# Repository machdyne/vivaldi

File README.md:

# Vivaldi Motherboard

Vivaldi is a host board that when paired with a [Sechzig](https://github.com/machdyne/sechzig) compute module can function as a personal server, network gateway or firewall.

This repo contains schematics, PCB layouts, pinouts and documentation.

Find more information on the [Vivaldi product page](https://machdyne.com/product/vivaldi-motherboard/).

## Using Vivaldi

Vivaldi requires a Sechzig module to function. **When inserting a Sechzig module, make sure that pin 2 on Vivaldi and pin 2 on the module are both on the same side.**

## Firmware

Mozart has a JTAG and USB CDC interface that are both accessible on the USB-C port. These interfaces are provided by a [fork of pico-dirtyJtag](https://github.com/machdyne/vivaldi/tree/main/firmware). You can update the RP2040 firmware by holding down the BOOT button and then applying power.

To build the firmware from source:

```
$ cd firmware/pico-dirtyJtag
$ mkdir build
$ cmake .. -DPICO_DEFAULT_BOOT_STAGE2_FILE=$PICO_SDK_PATH/src/rp2_common/boot_stage2/boot2_generic_03h.S
$ make
```

## Pinouts

### LVDS Port

Vivaldi has an experimental SATA-style LVDS port. SATA is not supported.

| Pin | Signal |
| --- | ------ |
| 1 | GND |
| 2 | DS2\_P |
| 3 | DS2\_N |
| 4 | GND |
| 5 | DS1\_P |
| 6 | DS1\_N |
| 7 | GND |

## Funding

This project was partially funded through the NGI0 Entrust Fund, a fund established by NLnet with financial support from the European Commission's Next Generation Internet programme.

## License

This project is released under the [CERN-OHL-P](LICENSE.txt) license.

Note: You can use these designs for commercial purposes but we ask that instead of producing exact clones, that you either replace our trademarks and logos with your own or add your own next to ours.

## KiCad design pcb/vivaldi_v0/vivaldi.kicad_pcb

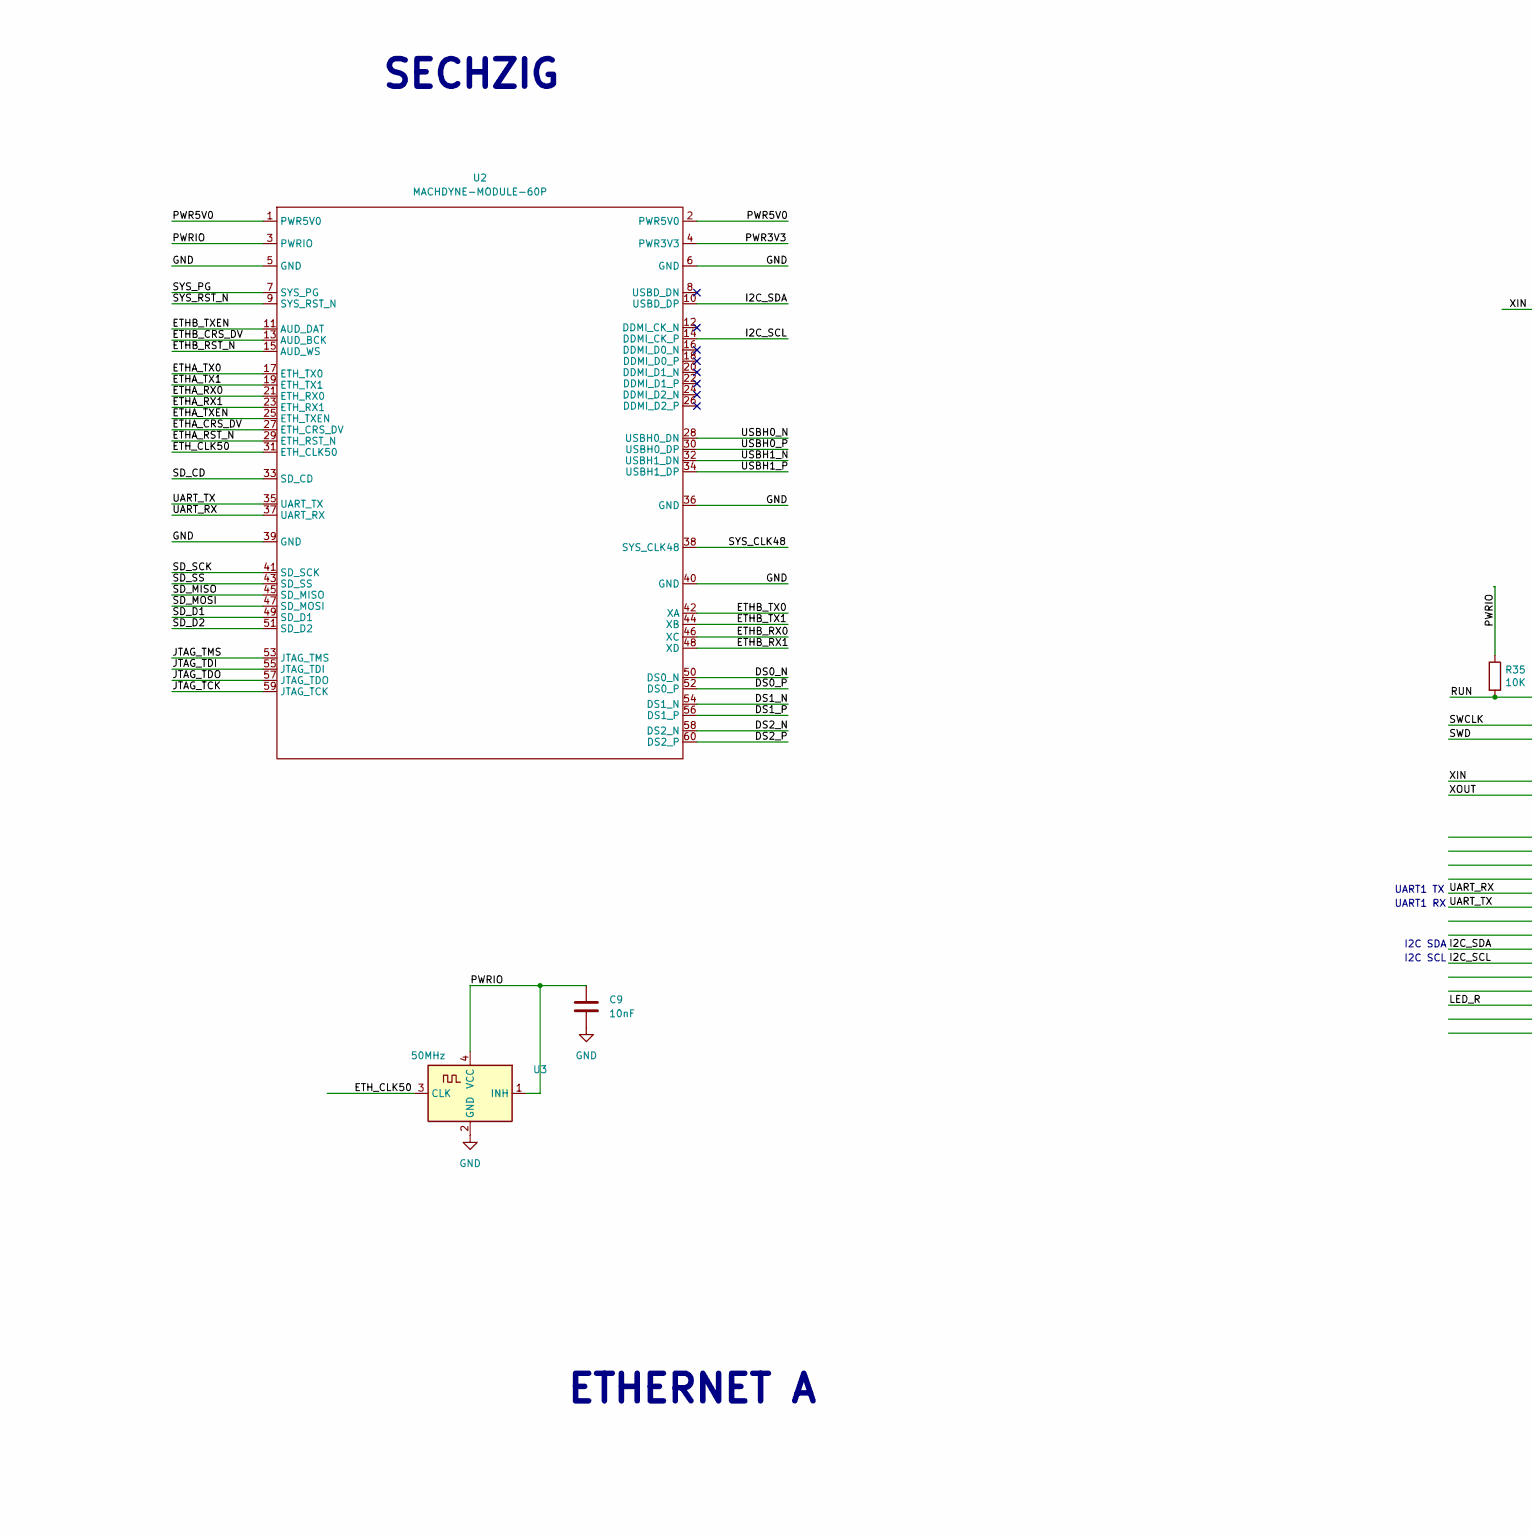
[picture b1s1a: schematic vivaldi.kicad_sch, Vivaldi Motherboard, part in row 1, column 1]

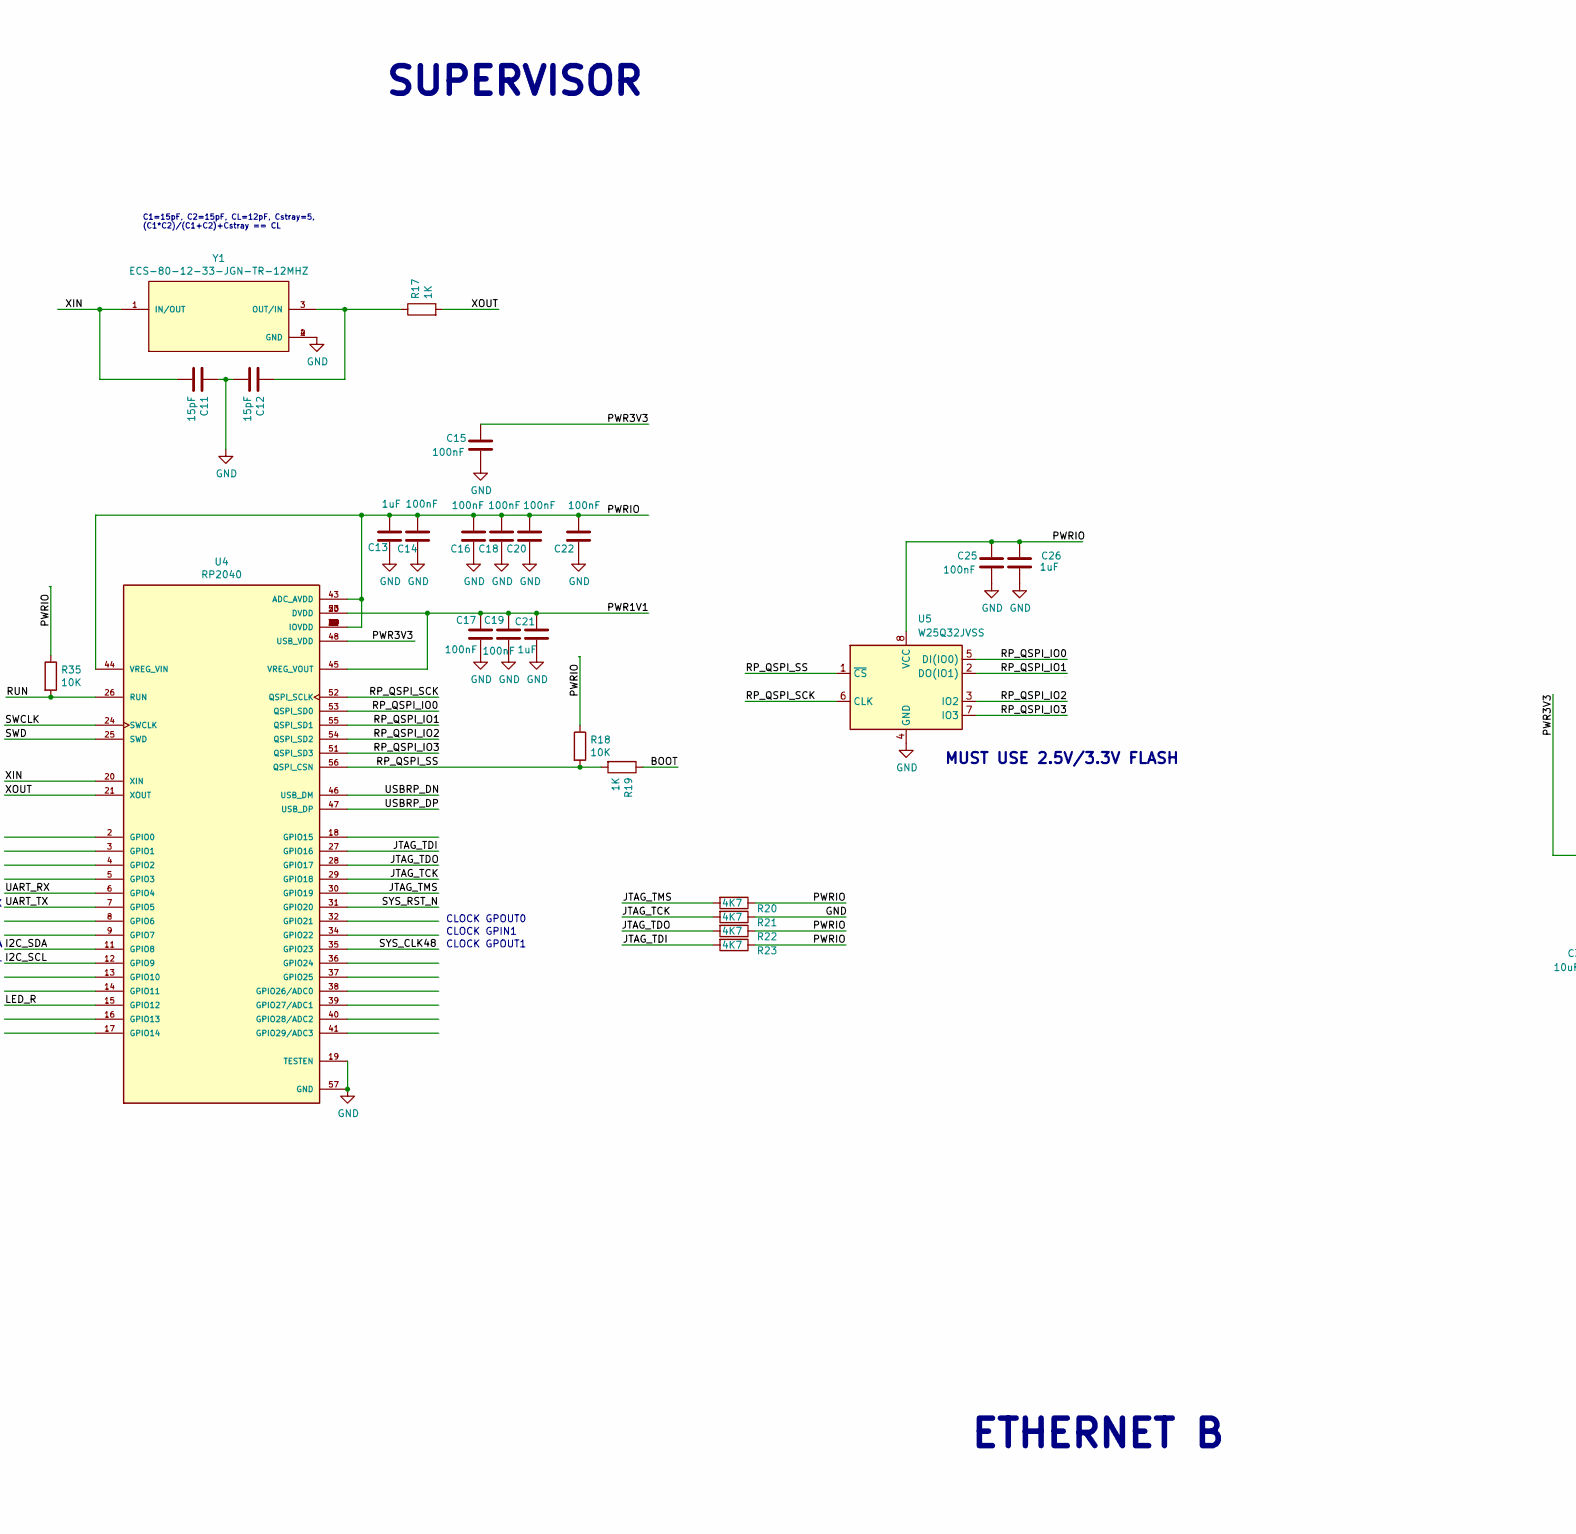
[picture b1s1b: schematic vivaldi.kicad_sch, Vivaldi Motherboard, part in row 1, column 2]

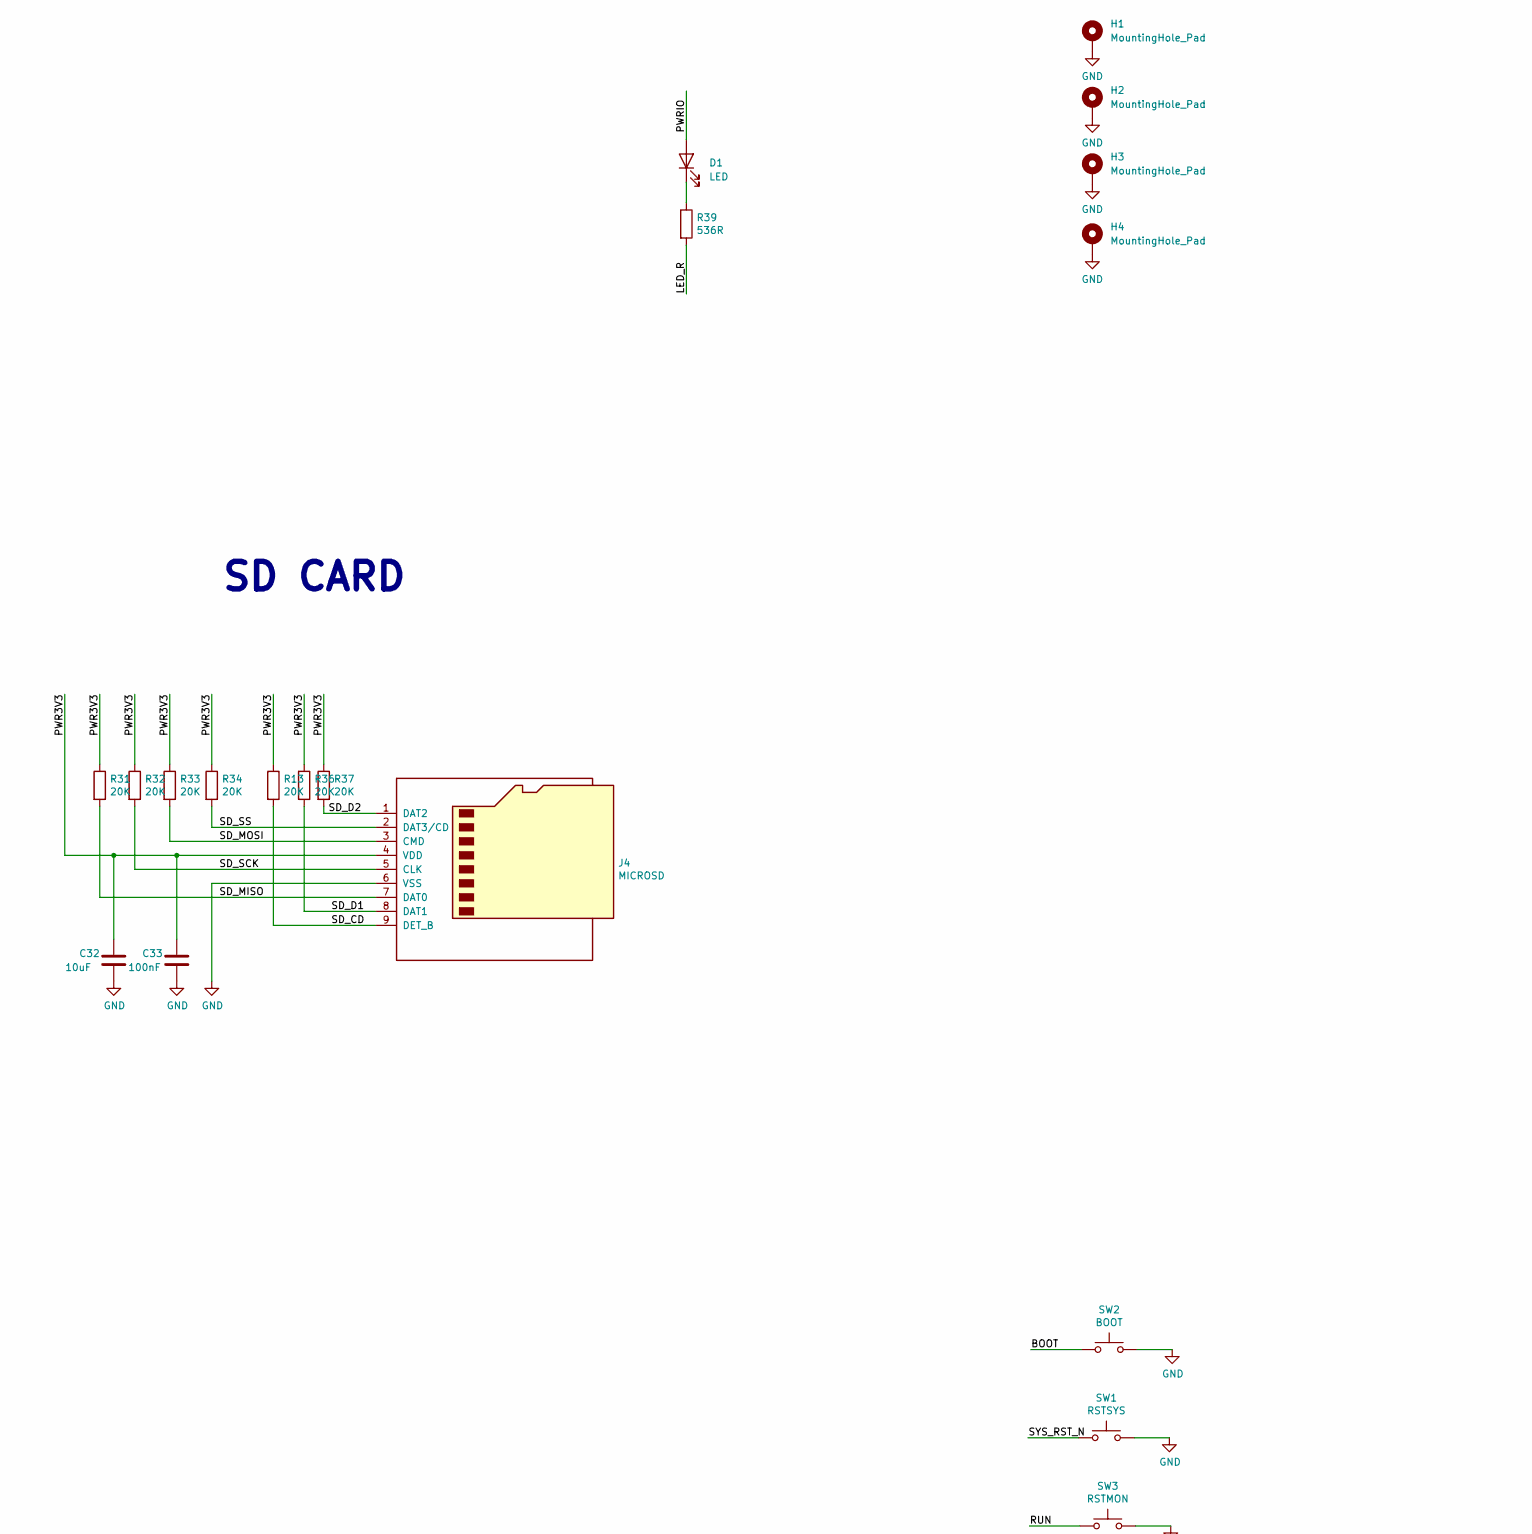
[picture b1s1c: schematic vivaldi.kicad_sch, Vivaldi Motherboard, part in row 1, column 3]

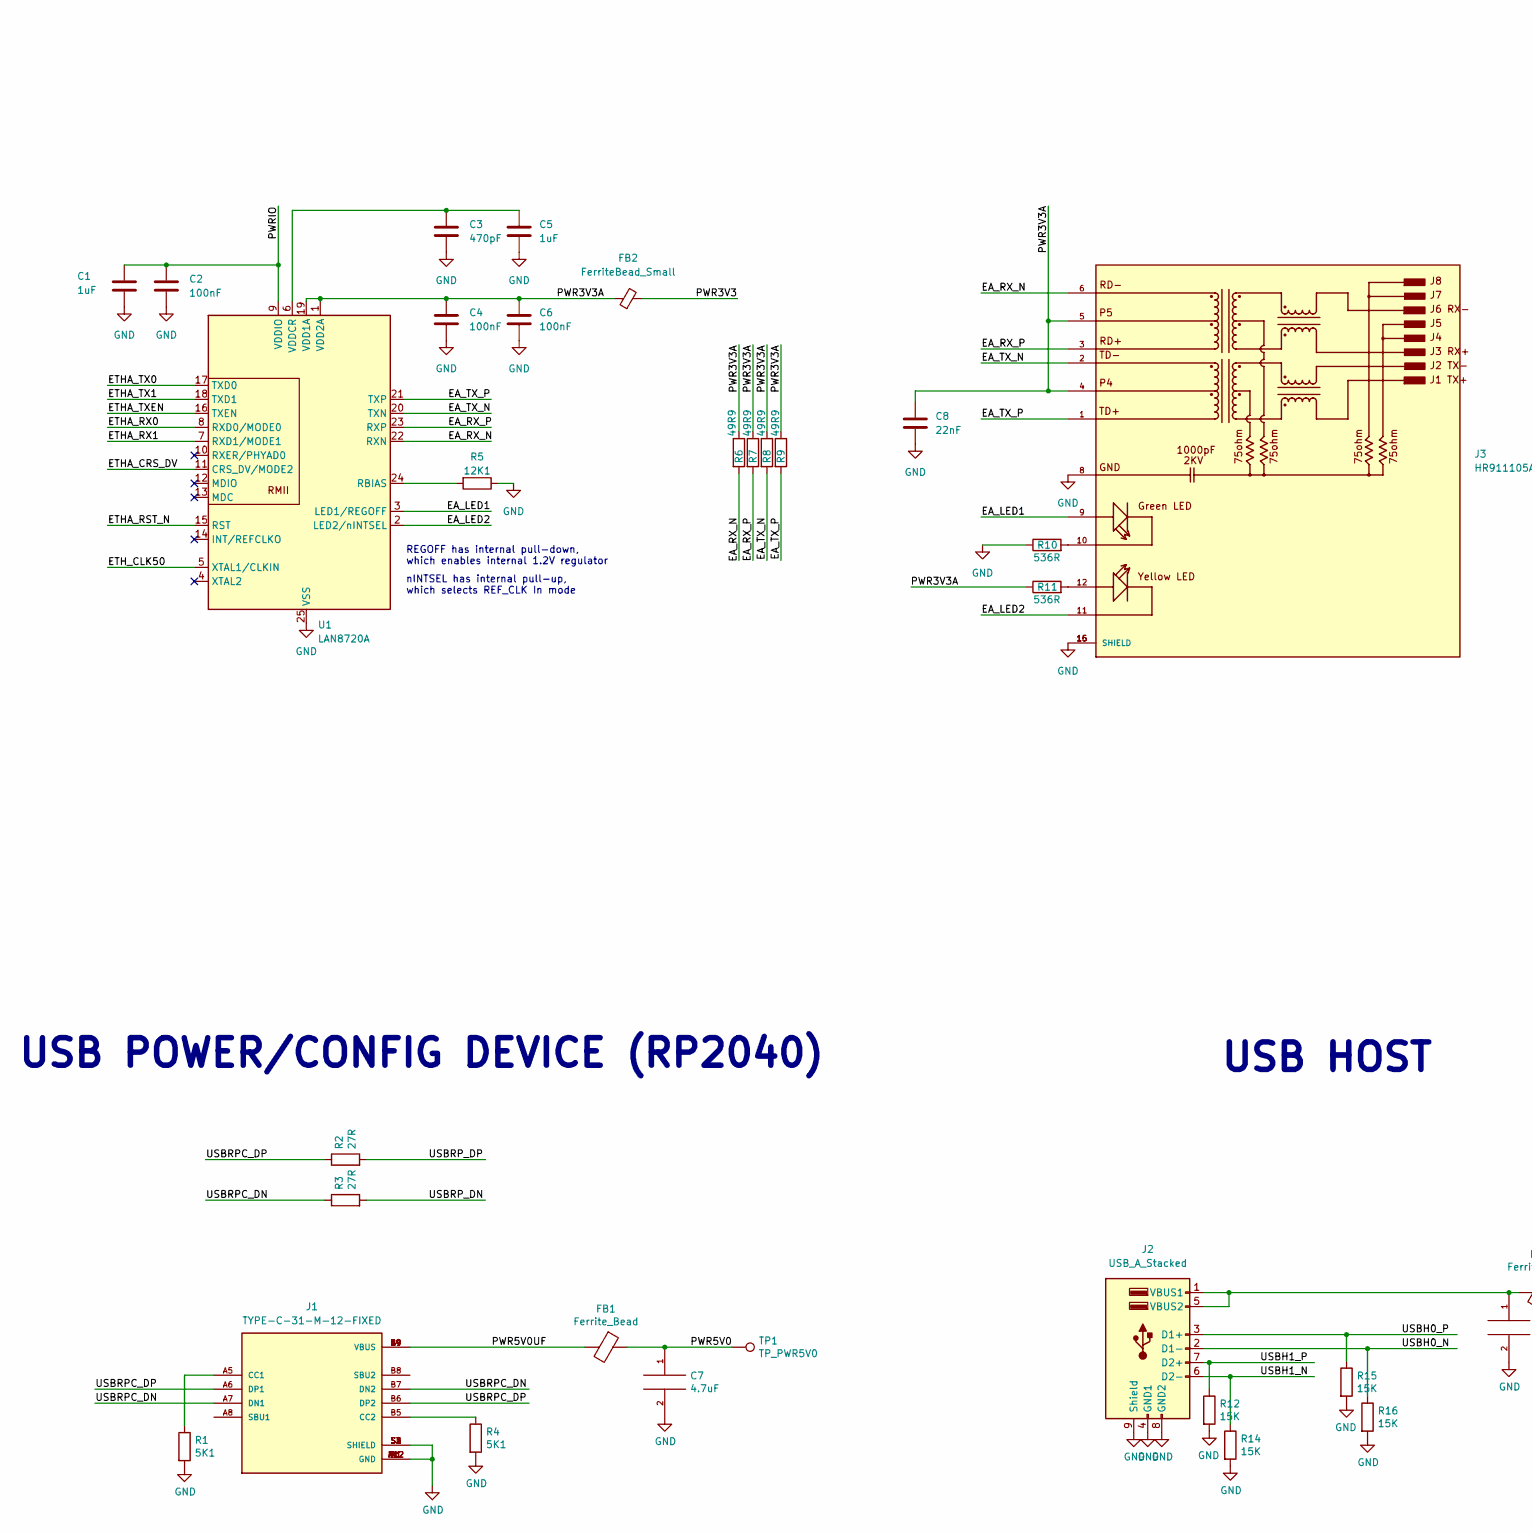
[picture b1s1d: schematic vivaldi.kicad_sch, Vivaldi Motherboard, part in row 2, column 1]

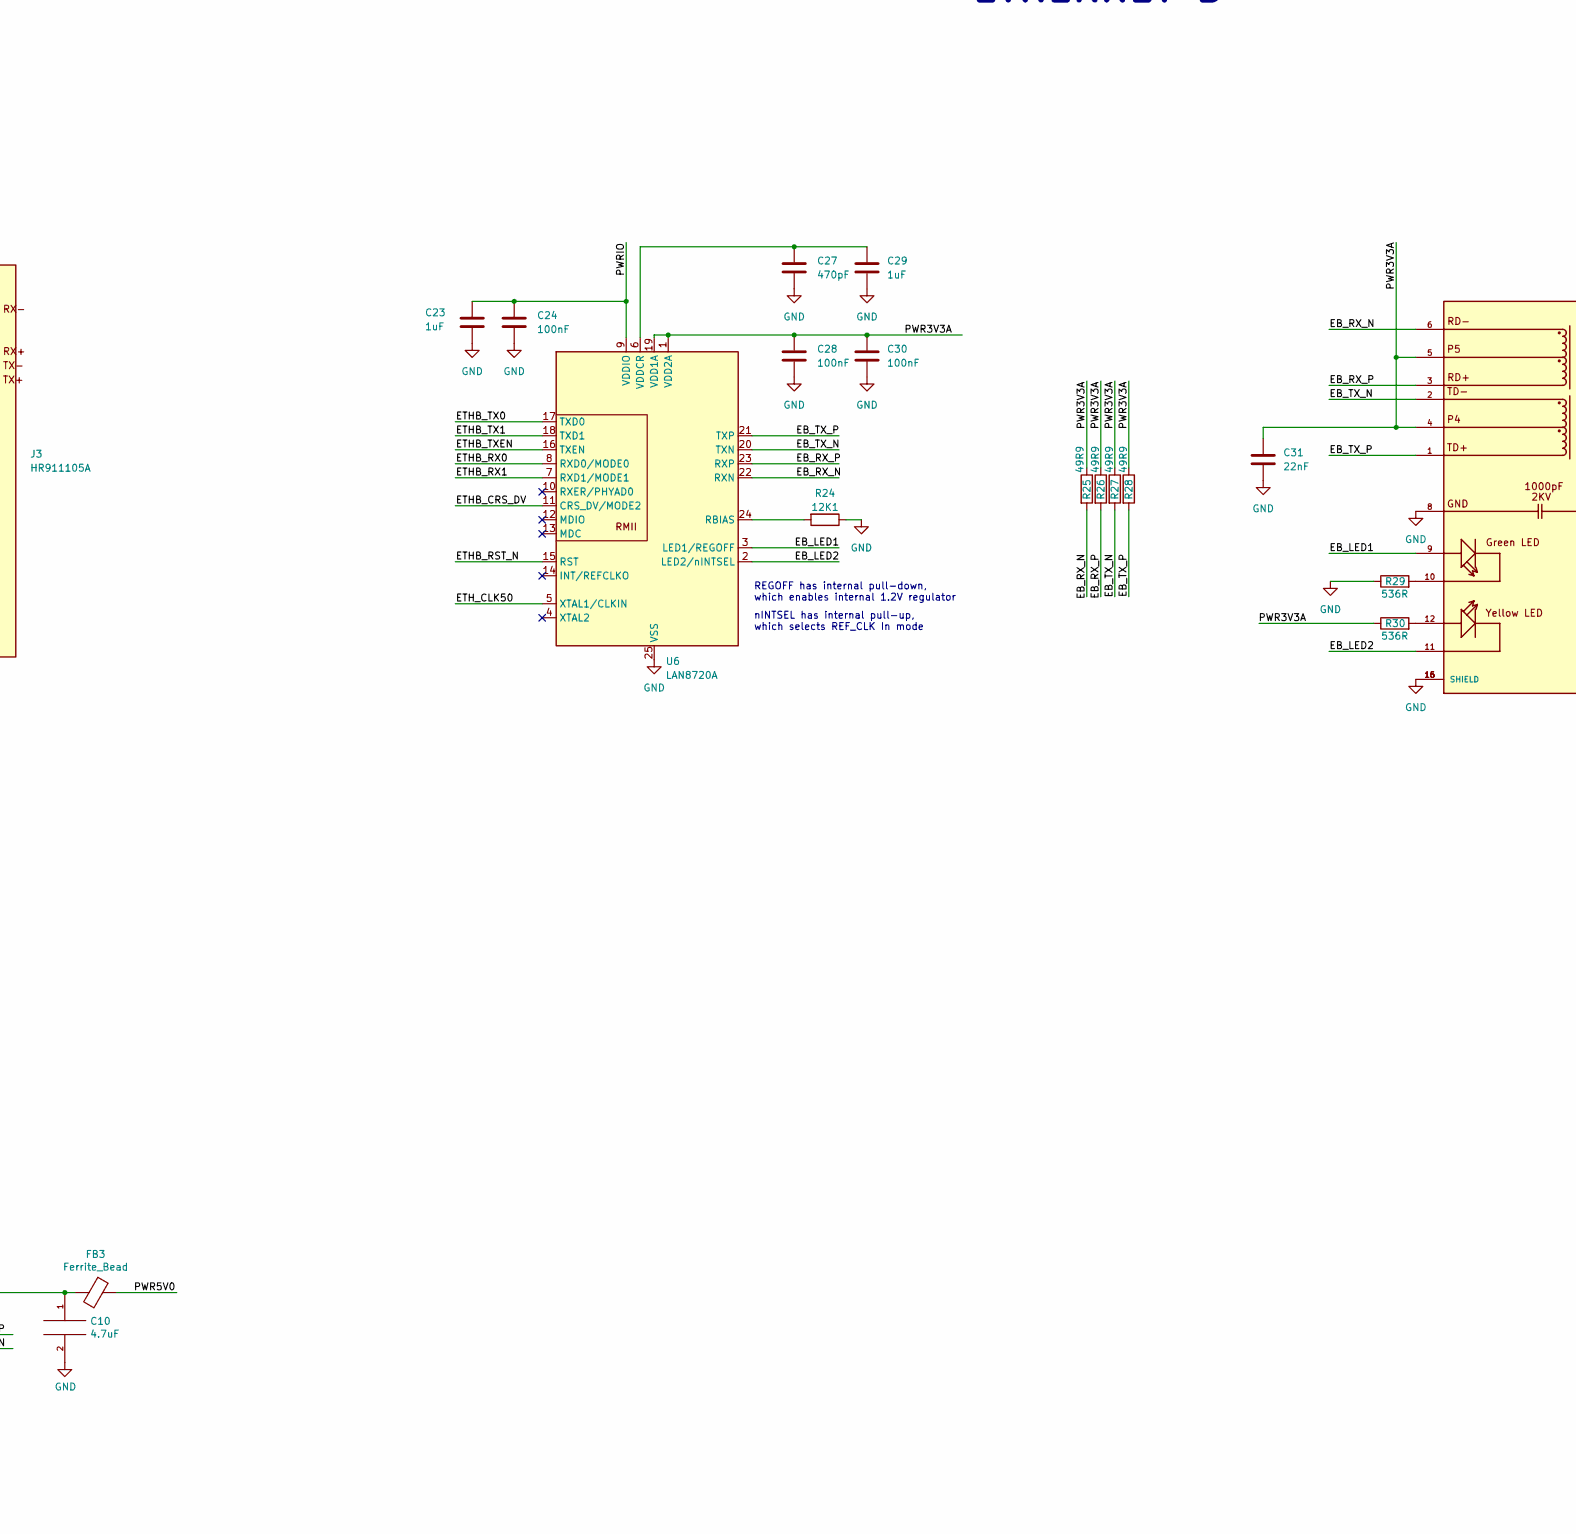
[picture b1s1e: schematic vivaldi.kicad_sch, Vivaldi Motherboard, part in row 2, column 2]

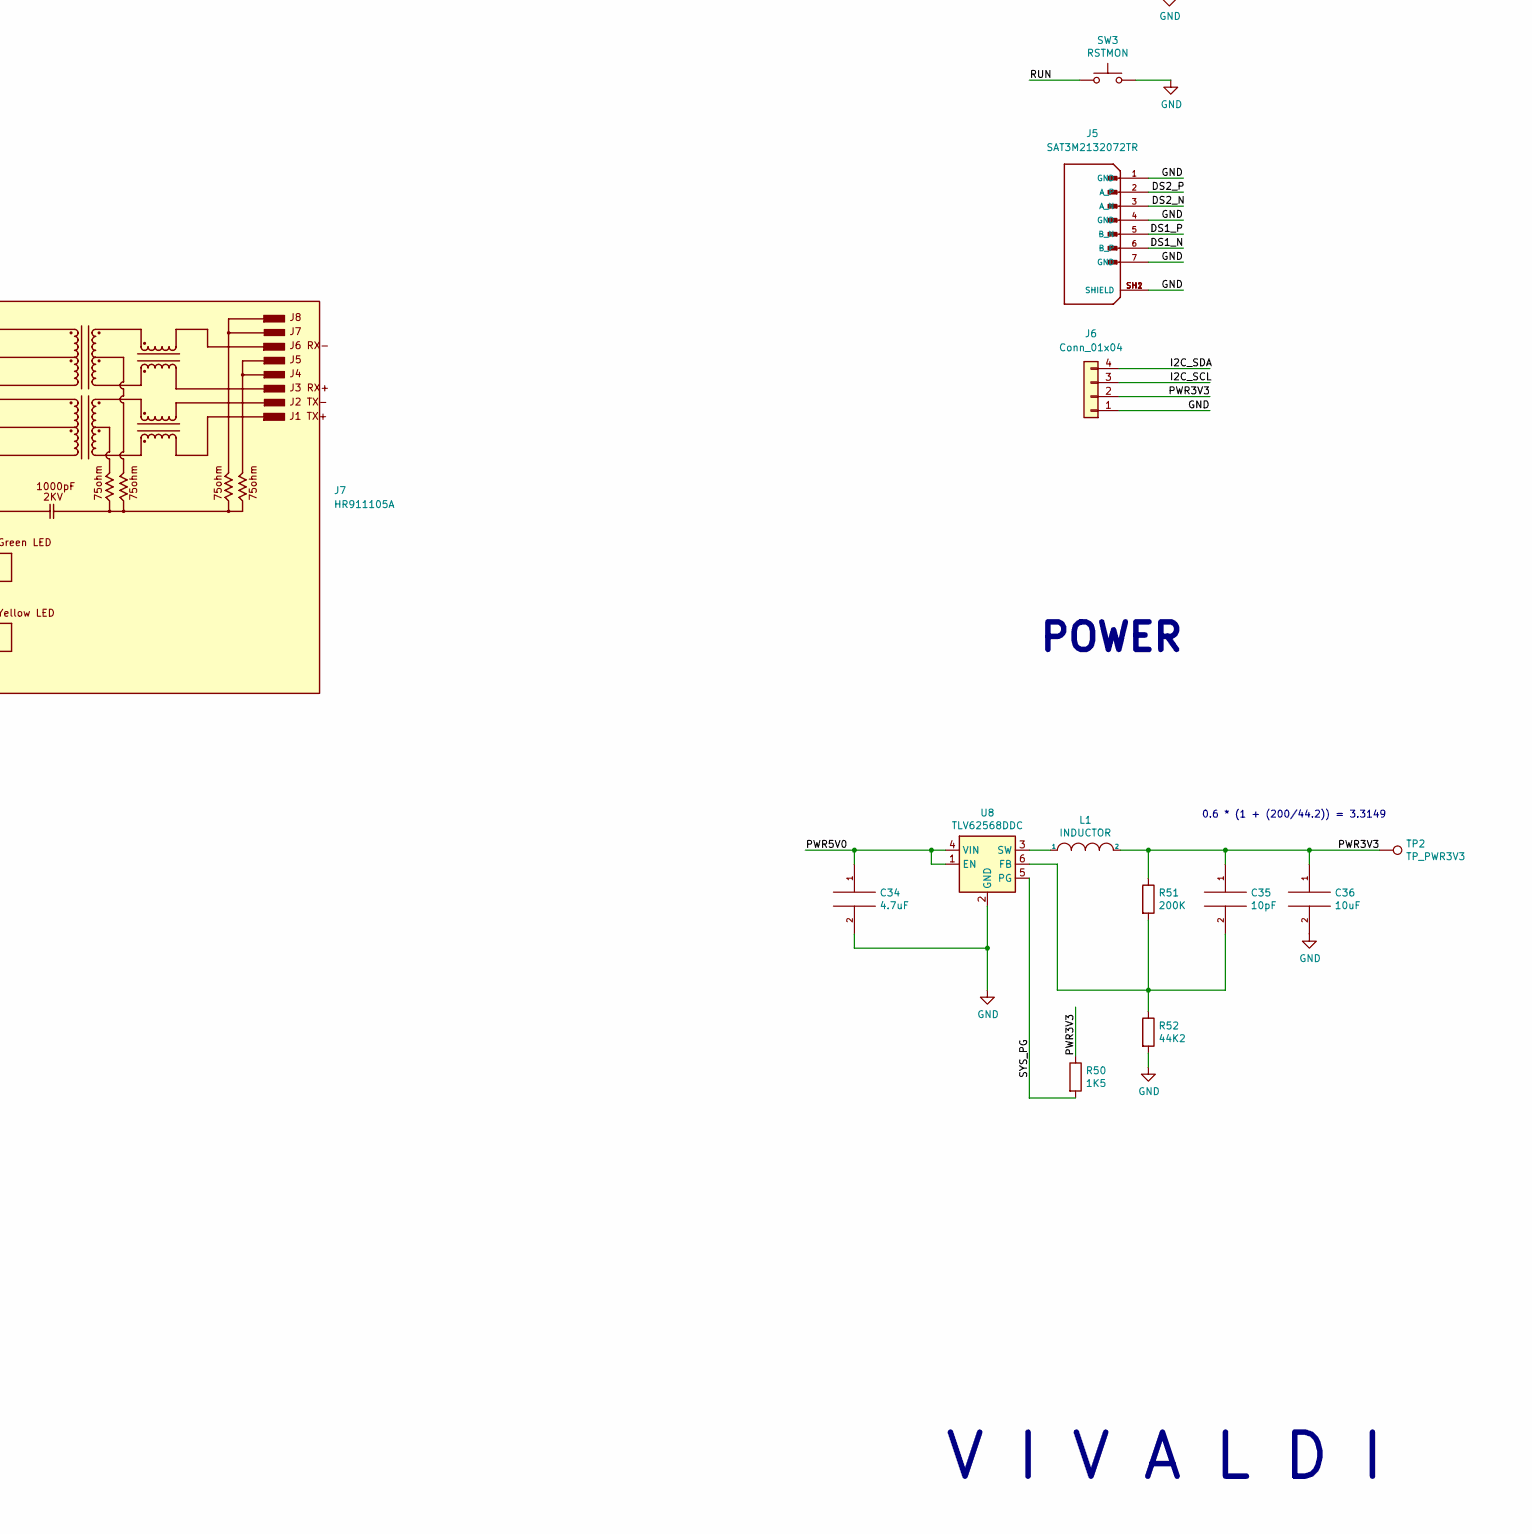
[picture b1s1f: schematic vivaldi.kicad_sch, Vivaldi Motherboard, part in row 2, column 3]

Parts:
C1, C5, C13, C21, C23, C26, C29: 1uF; C_0603_1608Metric
C2, C4, C6, C14, C15, C16, C17, C18, C19, C20, C22, C24, C25, C28, C30: 100nF; C_0603_1608Metric
C3, C27: 470pF; C_0603_1608Metric
C7, C10, C34: 4.7uF; C_0603_1608Metric
C8, C31: 22nF; C_0603_1608Metric
C9: 10nF; C_0603_1608Metric
C11, C12: 15pF; C_0603_1608Metric
C32: 10uF; R_0603_1608Metric
C33: 100nF; R_0603_1608Metric
C35: 10pF; C_0603_1608Metric
C36: 10uF; C_0603_1608Metric
D1: LED; LED_1206_3216Metric
FB1, FB3: Ferrite_Bead; R_0603_1608Metric
FB2: FerriteBead_Small; R_0603_1608Metric
H1, H2, H3, H4: MountingHole_Pad; MountingHole_3.2mm_M3_Pad
J1: TYPE-C-31-M-12-FIXED; USB_C_Receptacle_HRO_TYPE-C-31-M-12-BIG-PADS; PARTREV A
J2: USB_A_Stacked; USB_A_Wuerth_61400826021_Horizontal_Stacked
J3, J7: HR911105A; HANRUN_HR911105A; PARTREV A
J4: MICROSD; SDCARD
J5: SAT3M2132072TR; AMPHENOL_SAT3M2132072TR; PARTREV 1
J6: Conn_01x04; PinSocket_1x04_P2.54mm_Vertical
L1: INDUCTOR; L_0805_2012Metric
R1, R4: 5K1; R_0603_1608Metric
R2, R3: 27R; R_0603_1608Metric
R5, R24: 12K1; R_0603_1608Metric
R6, R7, R8, R9, R25, R26, R27, R28: 49R9; R_0603_1608Metric
R10, R11, R29, R30, R39: 536R; R_0603_1608Metric
R12, R14, R15, R16: 15K; R_0603_1608Metric
R13, R31, R32, R33, R34, R36, R37: 20K; R_0603_1608Metric
R17, R19: 1K; R_0603_1608Metric
R18, R35: 10K; R_0603_1608Metric
R20, R21, R22, R23: 4K7; R_0603_1608Metric
R50: 1K5; R_0603_1608Metric
R51: 200K; R_0603_1608Metric
R52: 44K2; R_0603_1608Metric
SW1: RSTSYS; SW_Tactile_SPST_Angled_PTS645Vx39-2LFS
SW2: BOOT; SW_Tactile_SPST_Angled_PTS645Vx39-2LFS
SW3: RSTMON; SW_Tactile_SPST_Angled_PTS645Vx39-2LFS
TP1: TP_PWR5V0; TestPoint_THTPad_D1.0mm_Drill0.5mm
TP2: TP_PWR3V3; TestPoint_THTPad_D1.0mm_Drill0.5mm
U1, U6: LAN8720A; QFN-24-1EP_4x4mm_P0.5mm_EP2.6x2.6mm
U2: MACHDYNE-MODULE-60P; MACHDYNE_EDGE_SOCKET_60P
U3: 50MHz; Oscillator_SMD_Kyocera_KC2520Z-4Pin_2.5x2.0mm
U4: RP2040; RP2040-QFN-56-OFFICIAL; PARTREV 1.6.1
U5: W25Q32JVSS; SOIC-8_3.9x4.9mm_P1.27mm
U8: TLV62568DDC; SOT-23-6
Y1: ECS-80-12-33-JGN-TR-12MHZ; XTAL_ECS-240-8-33-AGN-TR

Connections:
/BOOT: R19.1, SW2.1
/DS0_N: U2.50 (DS0_N)
/DS0_P: U2.52 (DS0_P)
/DS1_N: J5.6 (B_P), U2.54 (DS1_N)
/DS1_P: J5.5 (B_N), U2.56 (DS1_P)
/DS2_N: J5.3 (A_N), U2.58 (DS2_N)
/DS2_P: J5.2 (A_P), U2.60 (DS2_P)
/EA_LED1: J3.9, U1.3 (LED1/REGOFF)
/EA_LED2: J3.11, U1.2 (LED2/nINTSEL)
/EA_RX_N: J3.6, R6.2, U1.22 (RXN)
/EA_RX_P: J3.3, R7.2, U1.23 (RXP)
/EA_TX_N: J3.2, R8.2, U1.20 (TXN)
/EA_TX_P: J3.1, R9.2, U1.21 (TXP)
/EB_LED1: J7.9, U6.3 (LED1/REGOFF)
/EB_LED2: J7.11, U6.2 (LED2/nINTSEL)
/EB_RX_N: J7.6, R25.2, U6.22 (RXN)
/EB_RX_P: J7.3, R26.2, U6.23 (RXP)
/EB_TX_N: J7.2, R27.2, U6.20 (TXN)
/EB_TX_P: J7.1, R28.2, U6.21 (TXP)
/ETHA_CRS_DV: U1.11 (CRS_DV/MODE2), U2.27 (ETH_CRS_DV)
/ETHA_RST_N: U1.15 (RST), U2.29 (ETH_RST_N)
/ETHA_RX0: U1.8 (RXD0/MODE0), U2.21 (ETH_RX0)
/ETHA_RX1: U1.7 (RXD1/MODE1), U2.23 (ETH_RX1)
/ETHA_TX0: U1.17 (TXD0), U2.17 (ETH_TX0)
/ETHA_TX1: U1.18 (TXD1), U2.19 (ETH_TX1)
/ETHA_TXEN: U1.16 (TXEN), U2.25 (ETH_TXEN)
/ETHB_CRS_DV: U2.13 (AUD_BCK), U6.11 (CRS_DV/MODE2)
/ETHB_RST_N: U2.15 (AUD_WS), U6.15 (RST)
/ETHB_RX0: U2.46 (XC), U6.8 (RXD0/MODE0)
/ETHB_RX1: U2.48 (XD), U6.7 (RXD1/MODE1)
/ETHB_TX0: U2.42 (XA), U6.17 (TXD0)
/ETHB_TX1: U2.44 (XB), U6.18 (TXD1)
/ETHB_TXEN: U2.11 (AUD_DAT), U6.16 (TXEN)
/ETH_CLK50: U1.5 (XTAL1/CLKIN), U2.31 (ETH_CLK50), U3.3 (CLK), U6.5 (XTAL1/CLKIN)
/I2C_SCL: J6.3, U2.14 (DDMI_CK_P), U4.12 (GPIO9)
/I2C_SDA: J6.4, U2.10 (USBD_DP), U4.11 (GPIO8)
/JTAG_TCK: R21.2, U2.59 (JTAG_TCK), U4.29 (GPIO18)
/JTAG_TDI: R23.2, U2.55 (JTAG_TDI), U4.27 (GPIO16)
/JTAG_TDO: R22.2, U2.57 (JTAG_TDO), U4.28 (GPIO17)
/JTAG_TMS: R20.2, U2.53 (JTAG_TMS), U4.30 (GPIO19)
/LED_R: R39.2, U4.15 (GPIO12)
/PWR1V1: C17.1, C19.1, C21.1, U4.23 (DVDD), U4.45 (VREG_VOUT), U4.50 (DVDD)
/PWR3V3: C15.1, C32.1, C33.1, C35.1, C36.1, FB2.2, J4.4 (VDD), J6.2, L1.2, R13.1, R31.1, R32.1, R33.1, R34.1, R36.1, R37.1, R50.1, R51.1, TP2.1, U2.4 (PWR3V3), U4.48 (USB_VDD)
/PWR3V3A: C4.1, C6.1, C8.1, C28.1, C30.1, C31.1, FB2.1, J3.4, J3.5, J7.4, J7.5, R6.1, R7.1, R8.1, R9.1, R11.1, R25.1, R26.1, R27.1, R28.1, R30.1, U1.1 (VDD2A), U1.19 (VDD1A), U6.1 (VDD2A), U6.19 (VDD1A)
/PWR5V0: C7.1, C34.1, FB1.1, FB3.1, TP1.1, U2.1 (PWR5V0), U2.2 (PWR5V0), U8.1 (EN), U8.4 (VIN)
/PWR5V0UF: FB1.2, J1.A4 (VBUS), J1.A9 (VBUS), J1.B4 (VBUS), J1.B9 (VBUS)
/PWRIO: C1.1, C2.1, C9.1, C13.1, C14.1, C16.1, C18.1, C20.1, C22.1, C23.1, C24.1, C25.1, C26.1, D1.2 (A), R18.1, R20.1, R22.1, R23.1, R35.1, U1.9 (VDDIO), U2.3 (PWRIO), U3.1 (INH), U3.4 (VCC), U4.1 (IOVDD), U4.10 (IOVDD), U4.22 (IOVDD), U4.33 (IOVDD), U4.42 (IOVDD), U4.43 (ADC_AVDD), U4.44 (VREG_VIN), U4.49 (IOVDD), U5.8 (VCC), U6.9 (VDDIO)
/RP_QSPI_IO0: U4.53 (QSPI_SD0), U5.5 (DI(IO0))
/RP_QSPI_IO1: U4.55 (QSPI_SD1), U5.2 (DO(IO1))
/RP_QSPI_IO2: U4.54 (QSPI_SD2), U5.3 (IO2)
/RP_QSPI_IO3: U4.51 (QSPI_SD3), U5.7 (IO3)
/RP_QSPI_SCK: U4.52 (QSPI_SCLK), U5.6 (CLK)
/RP_QSPI_SS: R18.2, R19.2, U4.56 (QSPI_CSN), U5.1 (~CS)
/RUN: R35.2, SW3.1, U4.26 (RUN)
/SD_CD: J4.9 (DET_B), R13.2, U2.33 (SD_CD)
/SD_D1: J4.8 (DAT1), R36.2, U2.49 (SD_D1)
/SD_D2: J4.1 (DAT2), R37.2, U2.51 (SD_D2)
/SD_MISO: J4.7 (DAT0), R31.2, U2.45 (SD_MISO)
/SD_MOSI: J4.3 (CMD), R33.2, U2.47 (SD_MOSI)
/SD_SCK: J4.5 (CLK), R32.2, U2.41 (SD_SCK)
/SD_SS: J4.2 (DAT3/CD), R34.2, U2.43 (SD_SS)
/SWCLK: U4.24 (SWCLK)
/SWD: U4.25 (SWD)
/SYS_CLK48: U2.38 (SYS_CLK48), U4.35 (GPIO23)
/SYS_PG: R50.2, U2.7 (SYS_PG), U8.5 (PG)
/SYS_RST_N: SW1.1, U2.9 (SYS_RST_N), U4.31 (GPIO20)
/UART_RX: U2.37 (UART_RX), U4.6 (GPIO4)
/UART_TX: U2.35 (UART_TX), U4.7 (GPIO5)
/USBH0_N: J2.2 (D1-), R16.1, U2.28 (USBH0_DN)
/USBH0_P: J2.3 (D1+), R15.1, U2.30 (USBH0_DP)
/USBH1_N: J2.6 (D2-), R14.1, U2.32 (USBH1_DN)
/USBH1_P: J2.7 (D2+), R12.1, U2.34 (USBH1_DP)
/USBRPC_DN: J1.A7 (DN1), J1.B7 (DN2), R3.1
/USBRPC_DP: J1.A6 (DP1), J1.B6 (DP2), R2.1
/USBRP_DN: R3.2, U4.46 (USB_DM)
/USBRP_DP: R2.2, U4.47 (USB_DP)
/XIN: C11.2, U4.20 (XIN), Y1.1 (IN/OUT)
/XOUT: R17.2, U4.21 (XOUT)
GND: C1.2, C2.2, C3.2, C4.2, C5.2, C6.2, C7.2, C8.2, C9.2, C10.2, C11.1, C12.2, C13.2, C14.2, C15.2, C16.2, C17.2, C18.2, C19.2, C20.2, C21.2, C22.2, C23.2, C24.2, C25.2, C26.2, C27.2, C28.2, C29.2, C30.2, C31.2, C32.2, C33.2, C34.2, C36.2, H1.1, H2.1, H3.1, H4.1, J1.A1 (GND), J1.A12 (GND), J1.B1 (GND), J1.B12 (GND), J1.S1 (SHIELD), J1.S2 (SHIELD), J1.S3 (SHIELD), J1.S4 (SHIELD), J2.4 (GND1), J2.8 (GND2), J2.9 (Shield), J3.8, J3.15 (SHIELD), J3.16 (SHIELD), J4.6 (VSS), J5.1 (GND), J5.4 (GND), J5.7 (GND), J5.SH1 (SHIELD), J5.SH2 (SHIELD), J6.1, J7.8, J7.15 (SHIELD), J7.16 (SHIELD), R1.2, R4.2, R5.1, R10.1, R12.2, R14.2, R15.2, R16.2, R21.1, R24.1, R29.1, R52.2, SW1.2, SW2.2, SW3.2, U1.25 (VSS), U2.5 (GND), U2.6 (GND), U2.36 (GND), U2.39 (GND), U2.40 (GND), U3.2 (GND), U4.19 (TESTEN), U4.57 (GND), U5.4 (GND), U6.25 (VSS), U8.2 (GND), Y1.2 (GND), Y1.4 (GND)
unnamed: D1.1 (K), R39.1
unnamed: J1.A5 (CC1), R1.1
unnamed: J1.B5 (CC2), R4.1
unnamed: C10.1, FB3.2, J2.1 (VBUS1), J2.5 (VBUS2)
unnamed: J3.10, R10.2
unnamed: J3.12, R11.2
unnamed: J7.10, R29.2
unnamed: J7.12, R30.2
unnamed: R5.2, U1.24 (RBIAS)
unnamed: C3.1, C5.1, U1.6 (VDDCR)
unnamed: R24.2, U6.24 (RBIAS)
unnamed: C27.1, C29.1, U6.6 (VDDCR)
unnamed: C35.2, R51.2, R52.1, U8.6 (FB)
unnamed: L1.1, U8.3 (SW)
unnamed: C12.1, R17.1, Y1.3 (OUT/IN)

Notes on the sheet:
CLOCK GPOUT1
nINTSEL has internal pull-up, which selects REF_CLK In mode
V I V A L D I
0.6 * (1 + (200/44.2)) = 3.3149
SD CARD
REGOFF has internal pull-down, which enables internal 1.2V regulator
I2C SCL
MUST USE 2.5V/3.3V FLASH
C1=15pF, C2=15pF, CL=12pF, Cstray=5, (C1*C2)/(C1+C2)+Cstray == CL
UART1 TX
POWER
SECHZIG
I2C SDA
ETHERNET A
CLOCK GPIN1
USB POWER/CONFIG DEVICE (RP2040)
CLOCK GPOUT0
SUPERVISOR
ETHERNET B
USB HOST
UART1 RX

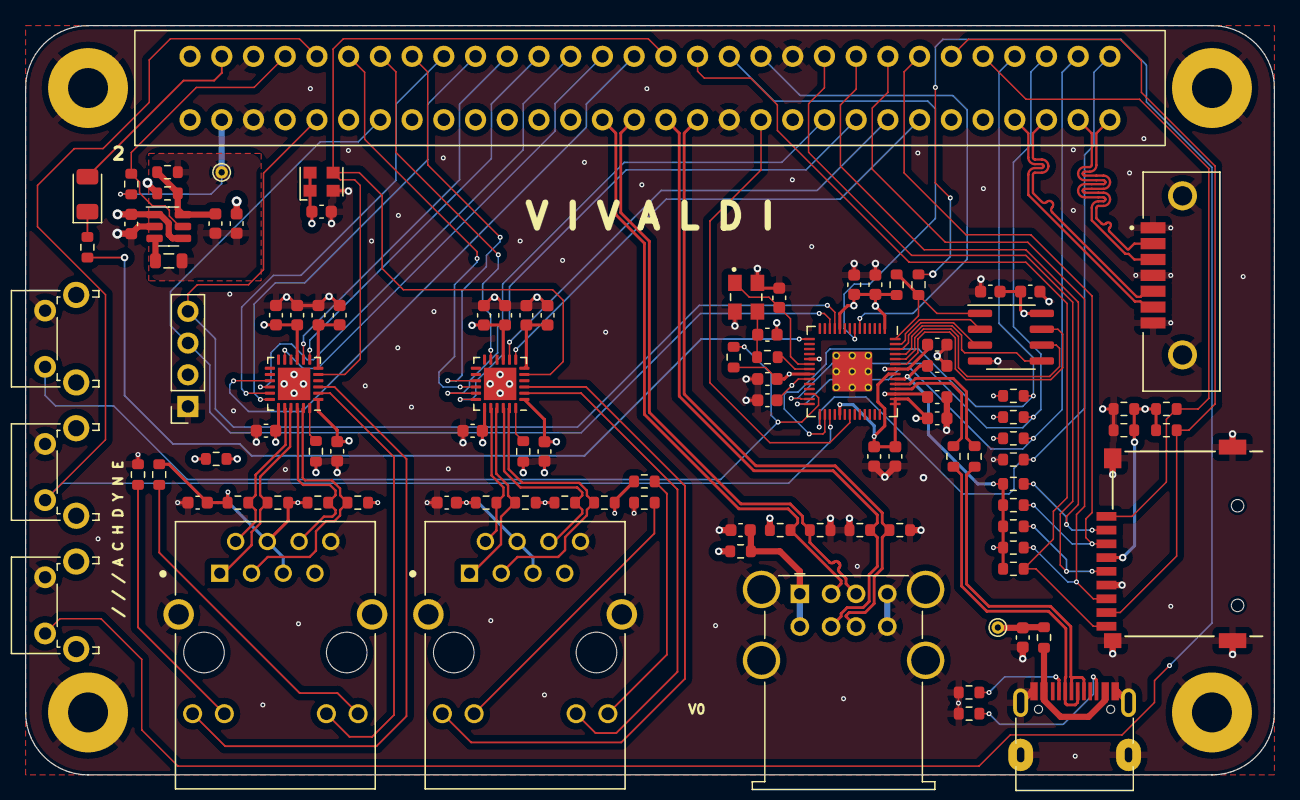
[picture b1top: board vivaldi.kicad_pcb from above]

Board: 4 copper layers, 100.0 x 60.0 mm, 106 parts (0 on the bottom side), 90 nets.

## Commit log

2024-03-06 add render
2024-03-12 add pcb
2024-03-12 remove irrelevant makefile
2024-03-15 add sechzig ml1.2 image
2024-03-19 update license

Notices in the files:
pcb/vivaldi_v0/vivaldi.kicad_sch:
Copyright © 2024 Lone Dynamics Corporation
